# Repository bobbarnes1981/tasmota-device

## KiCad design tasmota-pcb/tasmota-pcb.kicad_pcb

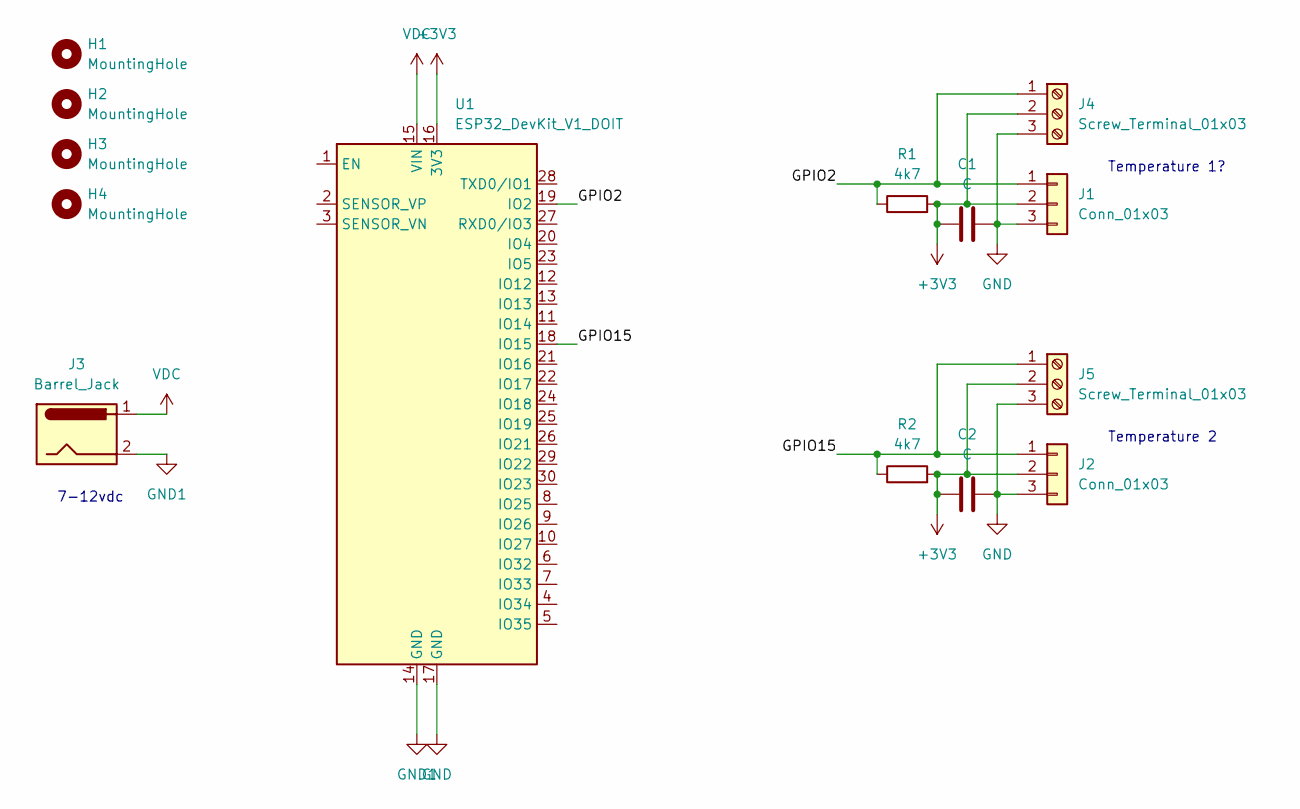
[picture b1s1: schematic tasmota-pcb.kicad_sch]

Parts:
C1, C2: C; CP_Radial_D4.0mm_P1.50mm
H1, H2, H3, H4: MountingHole; MountingHole_6.4mm_M6
J1, J2: Conn_01x03; PinHeader_1x03_P2.54mm_Horizontal
J3: Barrel_Jack; BarrelJack_Wuerth_6941xx301002
J4, J5: Screw_Terminal_01x03; TerminalBlock_Phoenix_MKDS-1,5-3_1x03_P5.00mm_Horizontal
R1, R2: 4k7; R_Axial_DIN0207_L6.3mm_D2.5mm_P10.16mm_Horizontal
U1: ESP32_DevKit_V1_DOIT; esp32_devkit_v1_doit

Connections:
+3V3: C1.1, C2.1, J1.2, J2.2, J4.2, J5.2, R1.2, R2.2, U1.16 (3V3)
/GPIO2: J1.1, J4.1, R1.1, U1.19 (IO2)
/GPIO15: J2.1, J5.1, R2.1, U1.18 (IO15)
GND: C1.2, C2.2, J1.3, J2.3, J4.3, J5.3, U1.17 (GND)
GND1: J3.2, U1.14 (GND)
VDC: J3.1, U1.15 (VIN)

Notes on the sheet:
Temperature 2
Temperature 1?
7-12vdc

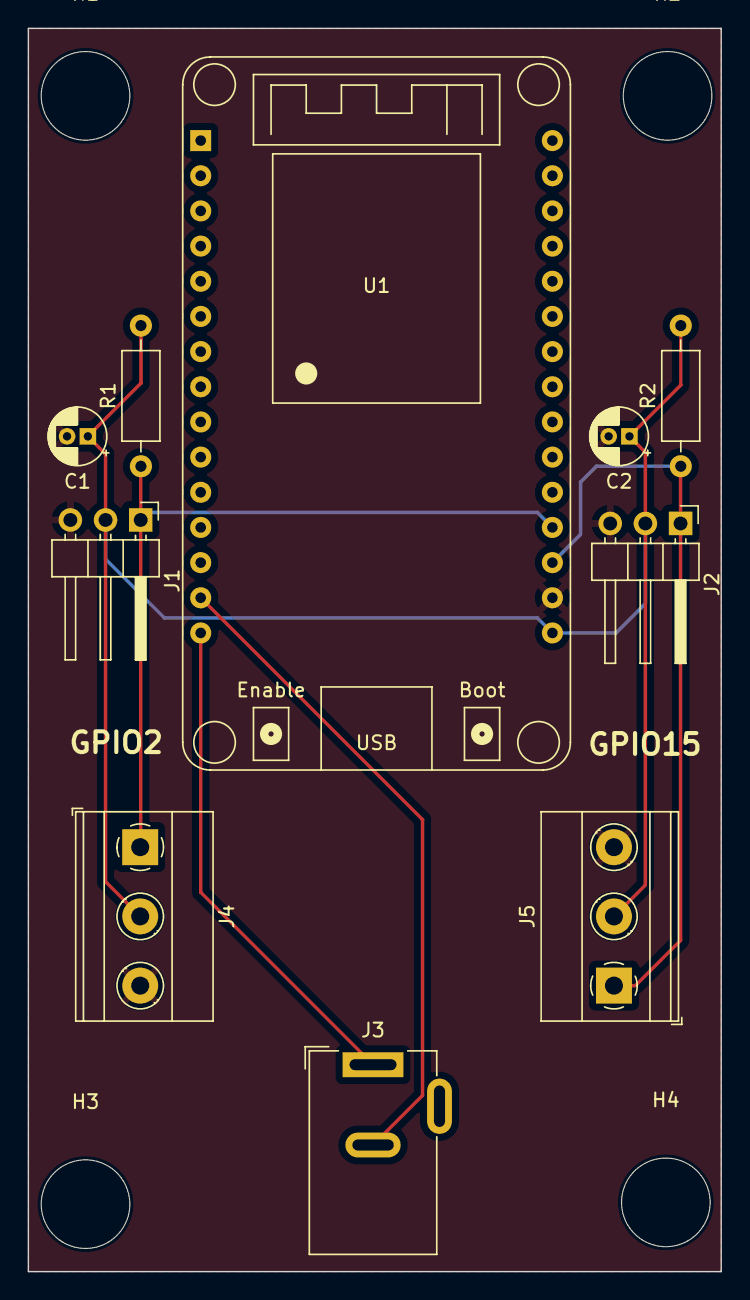
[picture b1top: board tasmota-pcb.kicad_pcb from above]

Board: 2 copper layers, 50.0 x 89.8 mm, 14 parts (0 on the bottom side), 6 nets.

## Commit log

2024-02-26 Add esp32 doit from https://gitlab.com/VictorLamoine/kicad
2024-02-26 Add some IO and power
2024-03-06 Layout pcb for case
2024-03-06 Add pcbway zip
